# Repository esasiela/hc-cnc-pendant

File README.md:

# hc-cnc-pendant

This repository is for the software required to run an Arduino-based CNC Pendant and the Python software bridge that connects the pendant to a Gcode sender.

## HC CNC Pendant 2020

As of January 2020, the project completed a major overhaul.  The prototype is retired having completed pilot testing, and the production model is LIVE.

The full journey is documented in full photographic glory at [Hedge Court](https://www.hedgecourt.com/robots/cncPendant/).

The source tree in this repository is divided into the production and prototype trees, since they are total rewrites rather than incremental modifications.

The 2020 revision includes:

* Host pendant application rewritten in Python.  

* State information (jog size and units) stored in host application, opening the door to multiple client devices/emulators.

* Built-in pendant emulator, allowing the user a GUI to enter any commands that the hardware pendant device supports.

* Hardware client pendant in beautifully crafted wood enclosure, containing custom manufactured PCB holding an Arduino Nano controller.

* bCNC compatible. UGS testing underway.

## HC CNC Pendant v2 (2017 prototype)

The rest of this document is obsolete and pertains to the pendant v2 model, a prototype that launched in 2017.

* The sender is the control software that is connected to the CNC machine.  Senders are outside the scope of this repository.  The client/host that are part of this repostiory interface with the sender of your choice.  Currently tested with Universal Gcode Sender (UGS) and bCNC. Via modifications to the properties file, can support any web ui that takes a simple line of Gcode via a request parameter.

* The client is the physical pendant device powered by an Arduino, connected to the host computer via USB.

* The host is a Java application that runs on the host computer.  It listens to the client over USB, and feeds G-Code to the sender (UGS, bCNC) via the sender's pendant web UI.

* It is common that the host will run on the same computer as the sender, however this is not required.  URL references to localhost can be changed to the remote address of the sender.

## hc-cnc-pendant-client

This directory contains the Arduino sketch that runs on the pendant device.

## hc-cnc-pendant-host

This directory contains the host application Java source and resources plus Maven .pom project descriptor.

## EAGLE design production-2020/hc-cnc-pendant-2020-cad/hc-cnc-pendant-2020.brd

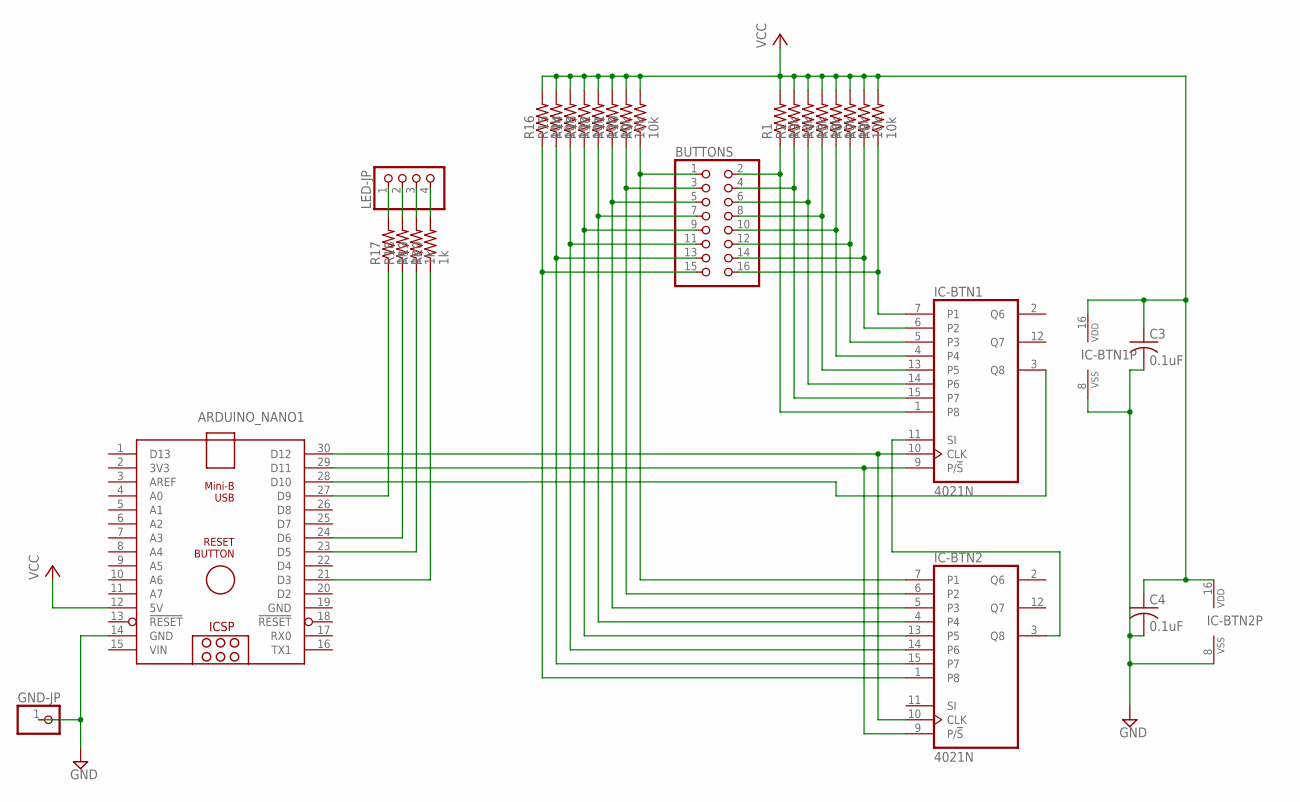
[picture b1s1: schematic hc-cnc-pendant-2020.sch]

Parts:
ARDUINO_NANO1: ARDUINO_NANO_HCARDUINO_NANO_NO_HOLE; ARDUINO_NANO_NO_HOLE
BUTTONS: PINHD-2X8; 2X08
C3, C4: 0.1uF; C025-030X050
GND-JP: PINHD-1X1; 1X01
IC-BTN1, IC-BTN2: 4021N; DIL16
LED-JP: PINHD-1X4; 1X04
R1, R2, R3, R4, R5, R6, R7, R8, R9, R10, R11, R12, R13, R14, R15, R16: 10k; 0309/12
R17, R18, R19, R20: 1k; 0309/12

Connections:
GND: ARDUINO_NANO1.14 (GND), ARDUINO_NANO1.19 (GND), C3.2, C4.2, GND-JP.1, IC-BTN1.8 (VSS), IC-BTN2.8 (VSS)
unnamed: ARDUINO_NANO1.30 (D12), IC-BTN1.10 (CLK), IC-BTN2.10 (CLK)
unnamed: ARDUINO_NANO1.29 (D11), IC-BTN1.9 (P/!S), IC-BTN2.9 (P/!S)
unnamed: BUTTONS.1, IC-BTN2.7 (P1), R9.1
unnamed: IC-BTN1.11 (SI), IC-BTN2.3 (Q8)
unnamed: ARDUINO_NANO1.28 (D10), IC-BTN1.3 (Q8)
unnamed: BUTTONS.3, IC-BTN2.6 (P2), R10.1
unnamed: BUTTONS.5, IC-BTN2.5 (P3), R11.1
unnamed: BUTTONS.7, IC-BTN2.4, R12.1
unnamed: BUTTONS.9, IC-BTN2.13 (P5), R13.1
unnamed: BUTTONS.11, IC-BTN2.14 (P6), R14.1
unnamed: BUTTONS.13, IC-BTN2.15 (P7), R15.1
unnamed: BUTTONS.15, IC-BTN2.1 (P8), R16.1
unnamed: BUTTONS.2, IC-BTN1.1 (P8), R1.1
unnamed: BUTTONS.4, IC-BTN1.15 (P7), R2.1
unnamed: BUTTONS.6, IC-BTN1.14 (P6), R3.1
unnamed: BUTTONS.8, IC-BTN1.13 (P5), R4.1
unnamed: BUTTONS.10, IC-BTN1.4, R5.1
unnamed: BUTTONS.12, IC-BTN1.5 (P3), R6.1
unnamed: BUTTONS.14, IC-BTN1.6 (P2), R7.1
unnamed: BUTTONS.16, IC-BTN1.7 (P1), R8.1
unnamed: LED-JP.1, R17.2
unnamed: LED-JP.2, R18.2
unnamed: LED-JP.3, R19.2
unnamed: LED-JP.4, R20.2
unnamed: ARDUINO_NANO1.21 (D3), R20.1
unnamed: ARDUINO_NANO1.23 (D5), R19.1
unnamed: ARDUINO_NANO1.24 (D6), R18.1
unnamed: ARDUINO_NANO1.27 (D9), R17.1
VCC: ARDUINO_NANO1.12 (5V), C3.1, C4.1, IC-BTN1.16 (VDD), IC-BTN2.16 (VDD), R1.2, R2.2, R3.2, R4.2, R5.2, R6.2, R7.2, R8.2, R9.2, R10.2, R11.2, R12.2, R13.2, R14.2, R15.2, R16.2
VIN: ARDUINO_NANO1.15 (VIN)

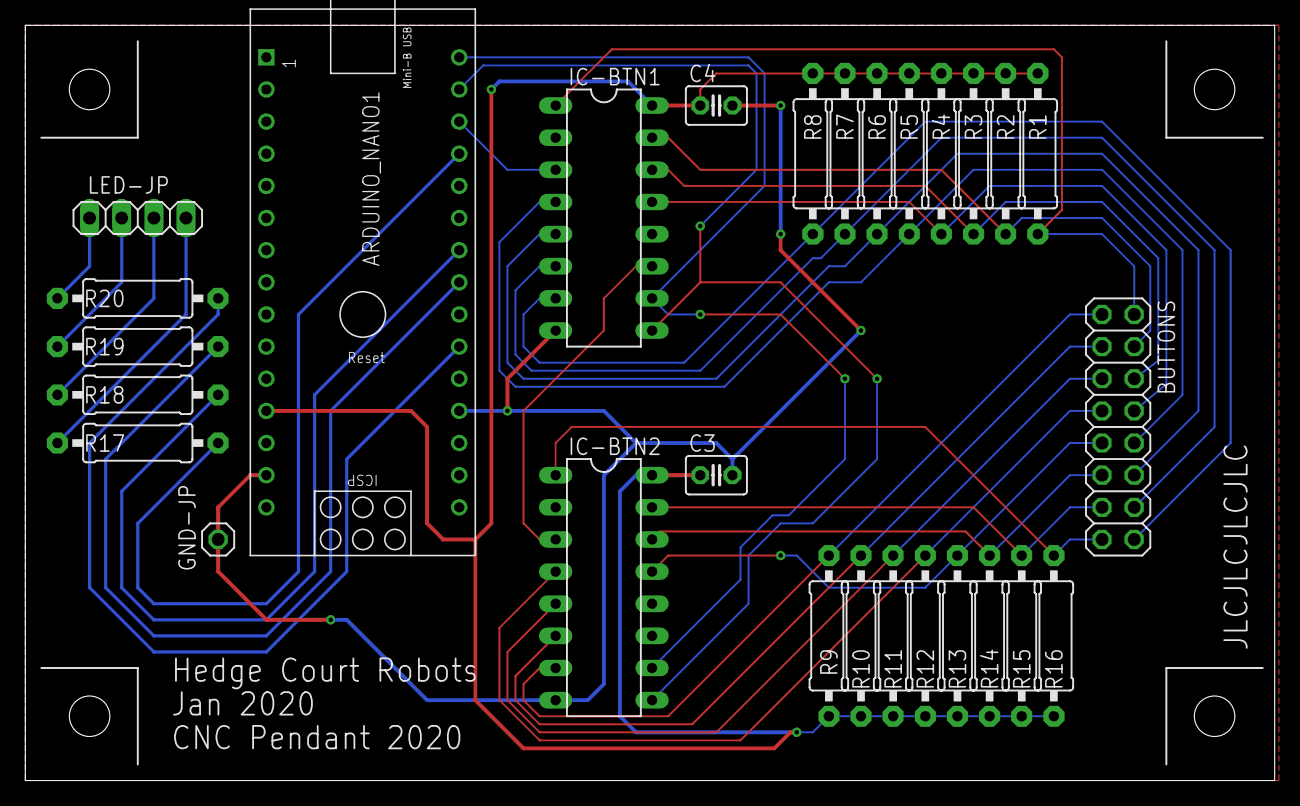
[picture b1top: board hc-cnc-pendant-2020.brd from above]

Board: 2 copper layers, 98.7 x 59.7 mm, 28 parts (0 on the bottom side), 30 nets.

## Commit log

2018-01-14 added overview
2018-02-21 added bCNC support
2020-01-17 2020 features functional with bCNC
2020-01-27 full featured except notify
2020-01-31 notify feature working with bcnc
2020-02-01 converted constants to enumerations
2020-10-13 Bump junit from 3.8.1 to 4.13.1 in /prototype-v2/hc-cnc-pendant-host
    Bumps [junit](https://github.com/junit-team/junit4) from 3.8.1 to 4.13.1.
    - [Release notes](https://github.com/junit-team/junit4/releases)
    - [Changelog](https://github.com/junit-team/junit4/blob/main/doc/ReleaseNotes4.13.1.md)
    - [Commits](https://github.com/junit-team/junit4/commits/r4.13.1)
2021-04-30 Bump urllib3 in /production-2020/hc-cnc-pendant-2020-python
    Bumps [urllib3](https://github.com/urllib3/urllib3) from 1.25.7 to 1.25.8.
    - [Release notes](https://github.com/urllib3/urllib3/releases)
    - [Changelog](https://github.com/urllib3/urllib3/blob/main/CHANGES.rst)
    - [Commits](https://github.com/urllib3/urllib3/compare/1.25.7...1.25.8)
2021-06-02 Bump urllib3 in /production-2020/hc-cnc-pendant-2020-python
    Bumps [urllib3](https://github.com/urllib3/urllib3) from 1.25.7 to 1.26.5.
    - [Release notes](https://github.com/urllib3/urllib3/releases)
    - [Changelog](https://github.com/urllib3/urllib3/blob/main/CHANGES.rst)
    - [Commits](https://github.com/urllib3/urllib3/compare/1.25.7...1.26.5)
    ---
    updated-dependencies:
2021-06-04 Bump httpclient in /prototype-v2/hc-cnc-pendant-host
    Bumps httpclient from 4.5.3 to 4.5.13.
    ---
    updated-dependencies:
    - dependency-name: org.apache.httpcomponents:httpclient
    dependency-type: direct:production
    ...
2022-12-08 Bump certifi in /production-2020/hc-cnc-pendant-2020-python
    Bumps [certifi](https://github.com/certifi/python-certifi) from 2019.11.28 to 2022.12.7.
    - [Release notes](https://github.com/certifi/python-certifi/releases)
    - [Commits](https://github.com/certifi/python-certifi/compare/2019.11.28...2022.12.07)
    ---
    updated-dependencies:
    - dependency-name: certifi
